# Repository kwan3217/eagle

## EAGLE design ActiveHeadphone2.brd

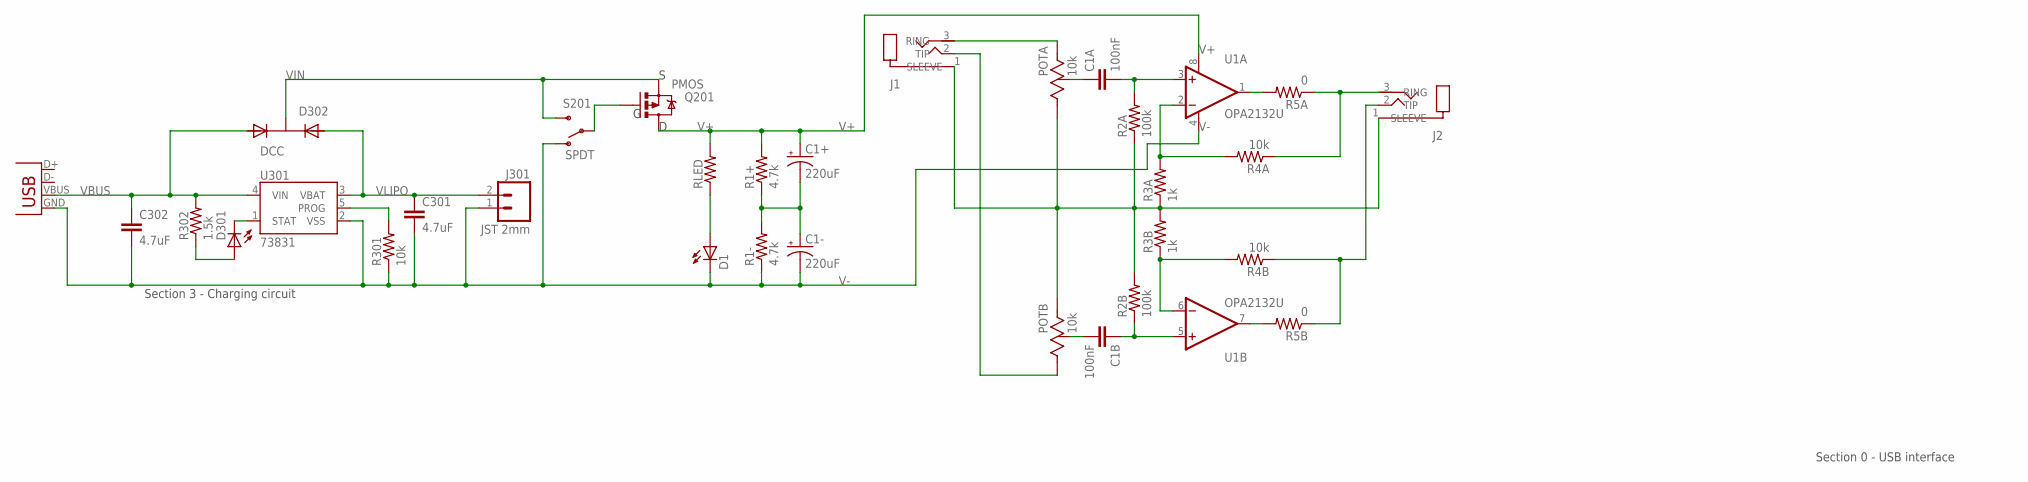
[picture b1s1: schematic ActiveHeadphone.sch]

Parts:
C1+, C1-: 220uF; EIA7343; DIGIKEY 399-5124-1-ND
C1A, C1B: 100nF; 0603-CAP
C301, C302: 4.7uF; 0603-CAP
D1, D301: RED; LED-0603
D302: DCC; SOT-23-3
J1, J2: 3.5mm; SJ1-3513-SMT
J003: USBSMD; USB-MINIB
J301: JST 2mm; JST-2-SMD
POTA: 10k; 3352T
POTB: 10k; 3352T
Q201: PMOS; SOT23-3
R1+, R1-: 4.7k; 0603-RES
R2A, R2B: 100k; 0603-RES
R3A, R3B: 1k; 0603-RES
R4A, R4B, R301: 10k; 0603-RES
R5A, R5B: 0; 0603-RES
R302: 1.5k; 0603-RES
RLED: RESISTOR0603-RES; 0603-RES
S201: SPDT; AYZ0202
U1: OPA2132U; SO08
U301: 73831; SOT23-5

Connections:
unnamed: C1A.2, R2A.2, U1.3 (+IN)
unnamed: D1.A, RLED.1
unnamed: J2.3 (RING), R4A.1, R5A.1
unnamed: J1.3 (RING), POTA.3 (CW)
unnamed: C1A.1, POTA.2 (WIPER)
unnamed: R5A.2, U1.1 (OUT)
unnamed: R3A.2, R4A.2, U1.2 (-IN)
unnamed: J1.2 (TIP), POTB.1 (CCW)
unnamed: C1B.2, POTB.2 (WIPER)
unnamed: C1B.1, R2B.1, U1.5 (+IN)
unnamed: R3B.1, R4B.2, U1.6 (-IN)
unnamed: R5B.2, U1.7 (OUT)
unnamed: J2.2 (TIP), R4B.1, R5B.1
unnamed: R301.2, U301.5 (PROG)
unnamed: C1+.C (-), C1-.A (+), R1+.1, R1-.2
unnamed: Q201.1 (G), S201.2
unnamed: D301.A, R302.1
unnamed: D301.C, U301.1 (STAT)
V+: C1+.A (+), Q201.3 (D), R1+.2, RLED.2, U1.8 (V+)
V-: C1-.C (-), C301.2, C302.2, D1.C, J003.GND, J301.1, R1-.1, R301.1, S201.1 (O), U1.4 (V-), U301.2 (VSS)
VBUS: C302.1, D302.1 (A1), J003.VBUS, R302.2, U301.4 (VIN)
VGND: J1.1 (SLEEVE), J2.1 (SLEEVE), POTA.1 (CCW), POTB.3 (CW), R2A.1, R2B.2, R3A.1, R3B.2
VIN: D302.3 (K), Q201.2 (S), S201.3 (S)
VLIPO: C301.1, D302.2 (A2), J301.2, U301.3 (VBAT)

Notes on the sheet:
Section 3 - Charging circuit
Section 0 - USB interface

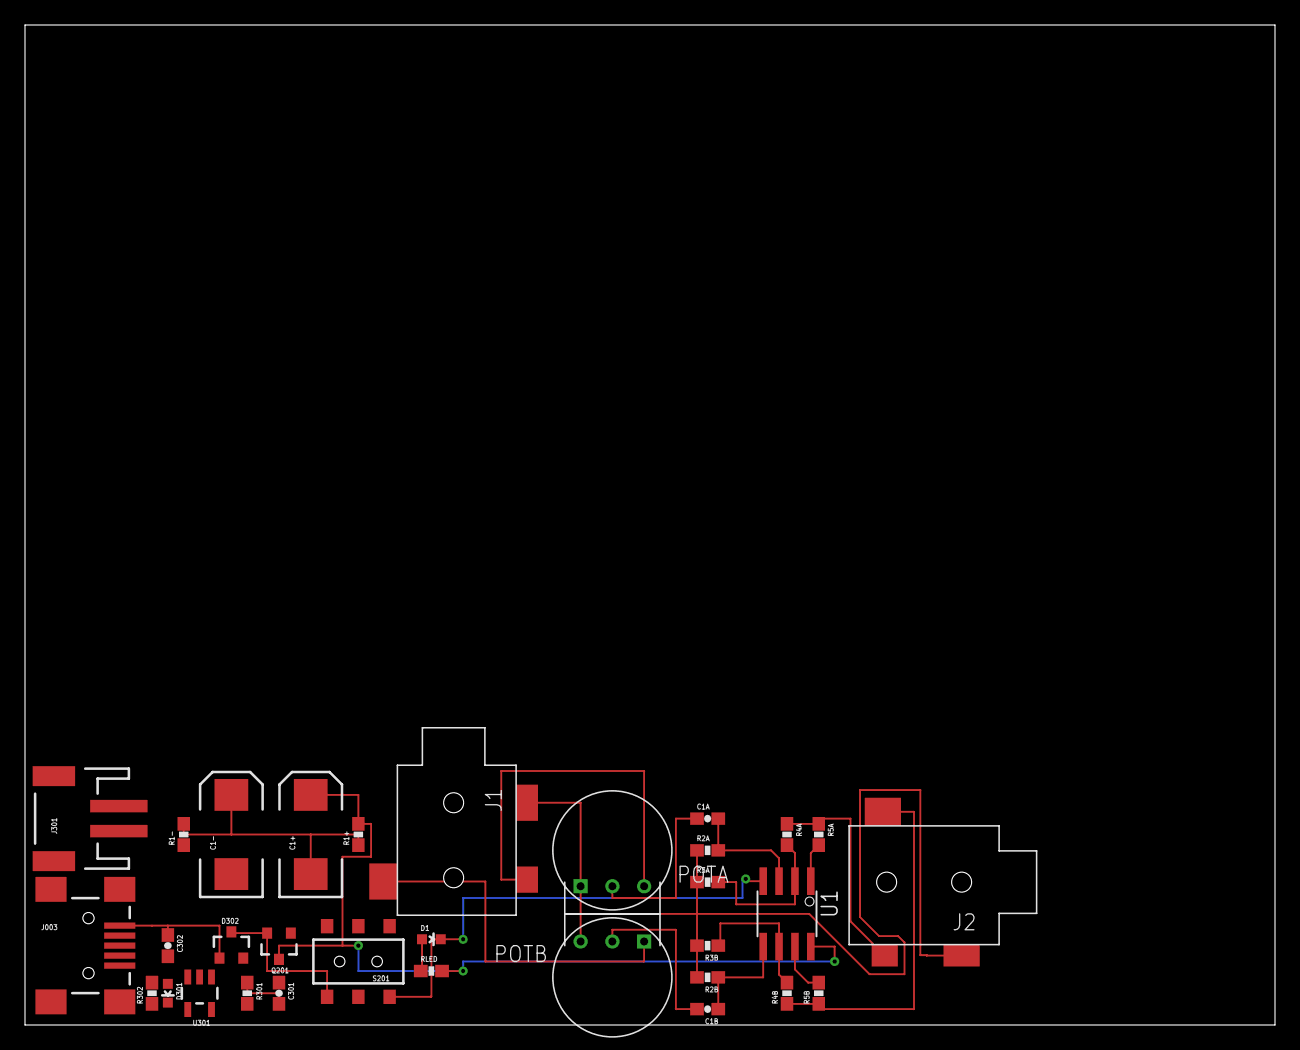
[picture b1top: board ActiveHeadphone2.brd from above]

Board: 2 copper layers, 100.0 x 80.0 mm, 32 parts (0 on the bottom side), 24 nets.

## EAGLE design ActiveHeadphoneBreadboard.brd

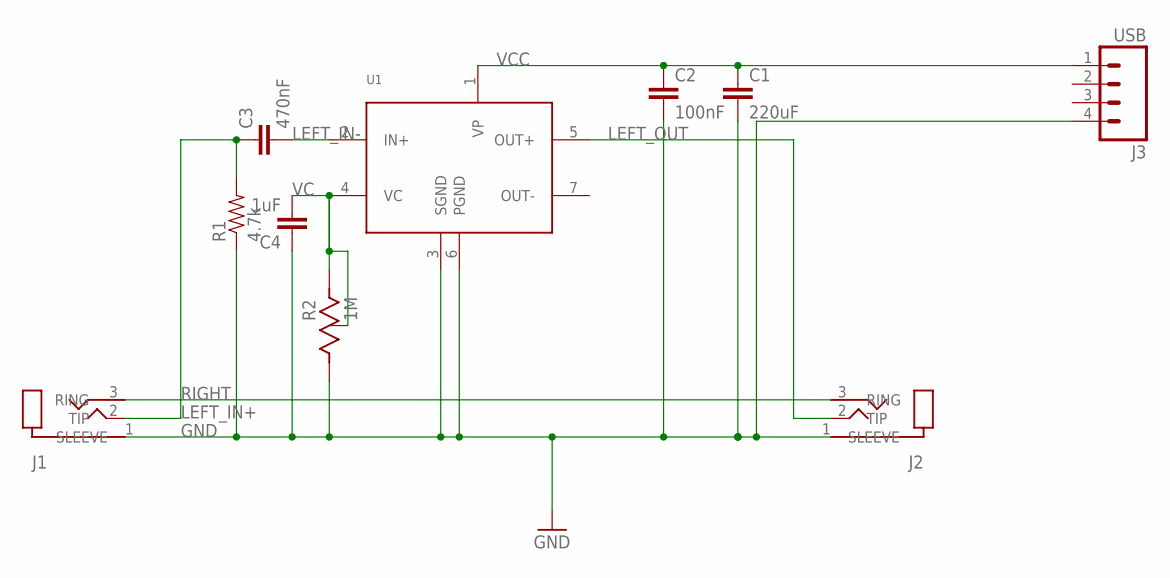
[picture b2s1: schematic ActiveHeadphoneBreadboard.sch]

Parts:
C1: 220uF; CAP-PTH-5MM
C2: 100nF; CAP-PTH-5MM
C3: 470nF; CAP-PTH-SMALL
C4: 1uF; CAP-PTH-SMALL
J1, J2: SJ1-35XXPTH; SJ1-3523N
J3: USB; 1X04
R1: 4.7k; AXIAL-0.4
R2: 1M; 3352T
U1: TDA7052; DIL-8

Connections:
GND: C1.2, C2.2, C4.1, J1.1 (SLEEVE), J2.1 (SLEEVE), J3.4, R1.P$1 (1), R2.1 (CCW), U1.3 (SGND), U1.6 (PGND)
LEFT_IN+: C3.1, J1.2 (TIP), R1.P$2 (2)
LEFT_IN-: C3.2, U1.2 (IN+)
LEFT_OUT: J2.2 (TIP), U1.5 (OUT+)
RIGHT: J1.3 (RING), J2.3 (RING)
VC: C4.2, R2.2 (WIPER), R2.3 (CW), U1.4 (VC)
VCC: C1.1, C2.1, J3.1, U1.1 (VP)

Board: 2 copper layers, 10 parts (0 on the bottom side), 7 nets, no tracks yet.

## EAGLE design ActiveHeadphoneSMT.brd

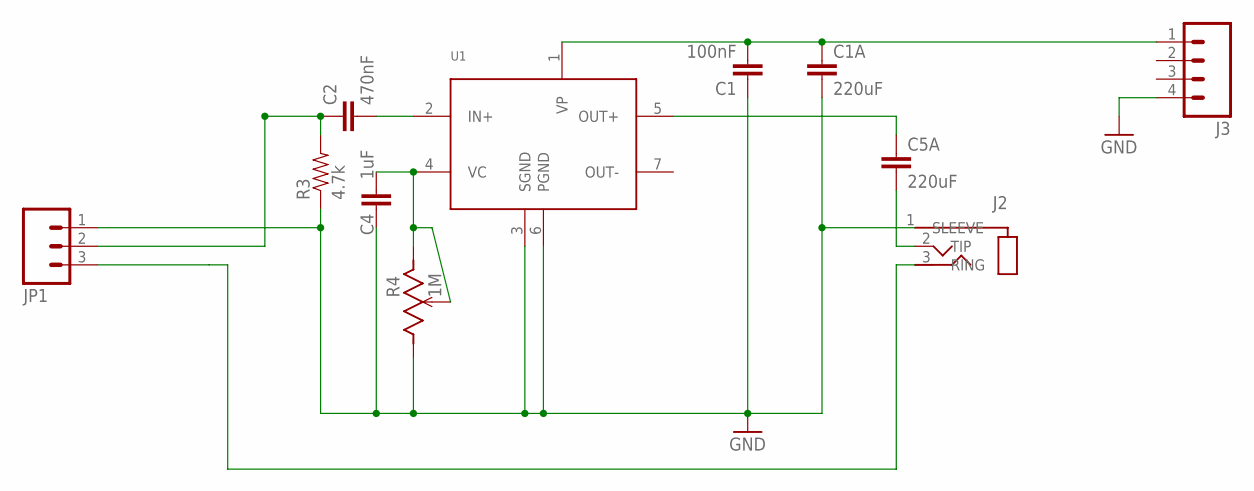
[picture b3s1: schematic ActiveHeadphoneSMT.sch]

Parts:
C1: 100nF; 0603-CAP
C1A, C5A: 220uF; CAP-PTH-5MM
C2: 470nF; 0603-CAP
C4: 1uF; 0603-CAP
J2: SJ1-35XXPTH; SJ1-3523N
J3: M04PTH; 1X04
JP1: M03PTH; 1X03
R3: 4.7k; 0603-RES
R4: 1M; 3352T
U1: TDA7052; DIL-8

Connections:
GND: C1.1, C1A.2, C4.1, J2.1 (SLEEVE), J3.4, JP1.1, R3.1, R4.1 (CCW), U1.3 (SGND), U1.6 (PGND)
unnamed: C2.2, U1.2 (IN+)
unnamed: C2.1, JP1.2, R3.2
unnamed: C5A.2, J2.2 (TIP)
unnamed: C4.2, R4.2 (WIPER), R4.3 (CW), U1.4 (VC)
unnamed: C1.2, C1A.1, J3.1, U1.1 (VP)
unnamed: C5A.1, U1.5 (OUT+)
unnamed: J2.3 (RING), JP1.3

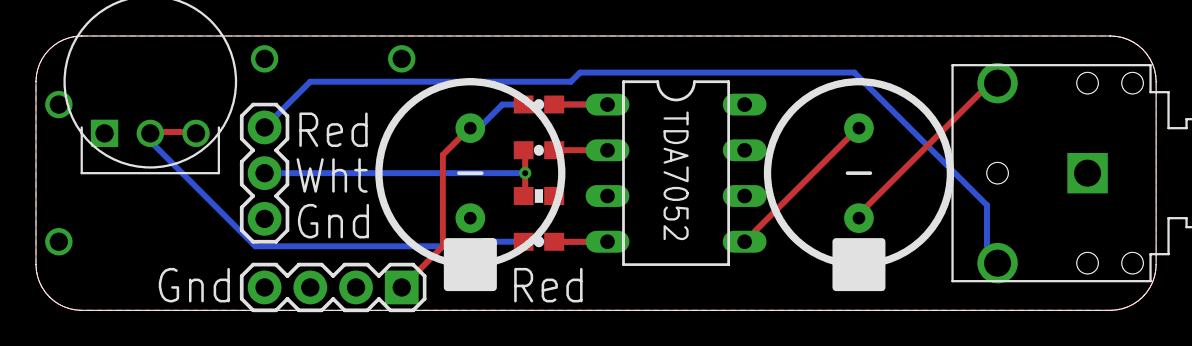
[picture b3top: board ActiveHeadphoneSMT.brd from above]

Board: 2 copper layers, 62.2 x 15.2 mm, 12 parts (1 on the bottom side), 8 nets.

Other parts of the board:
U$1: KWAN_CIRCLE

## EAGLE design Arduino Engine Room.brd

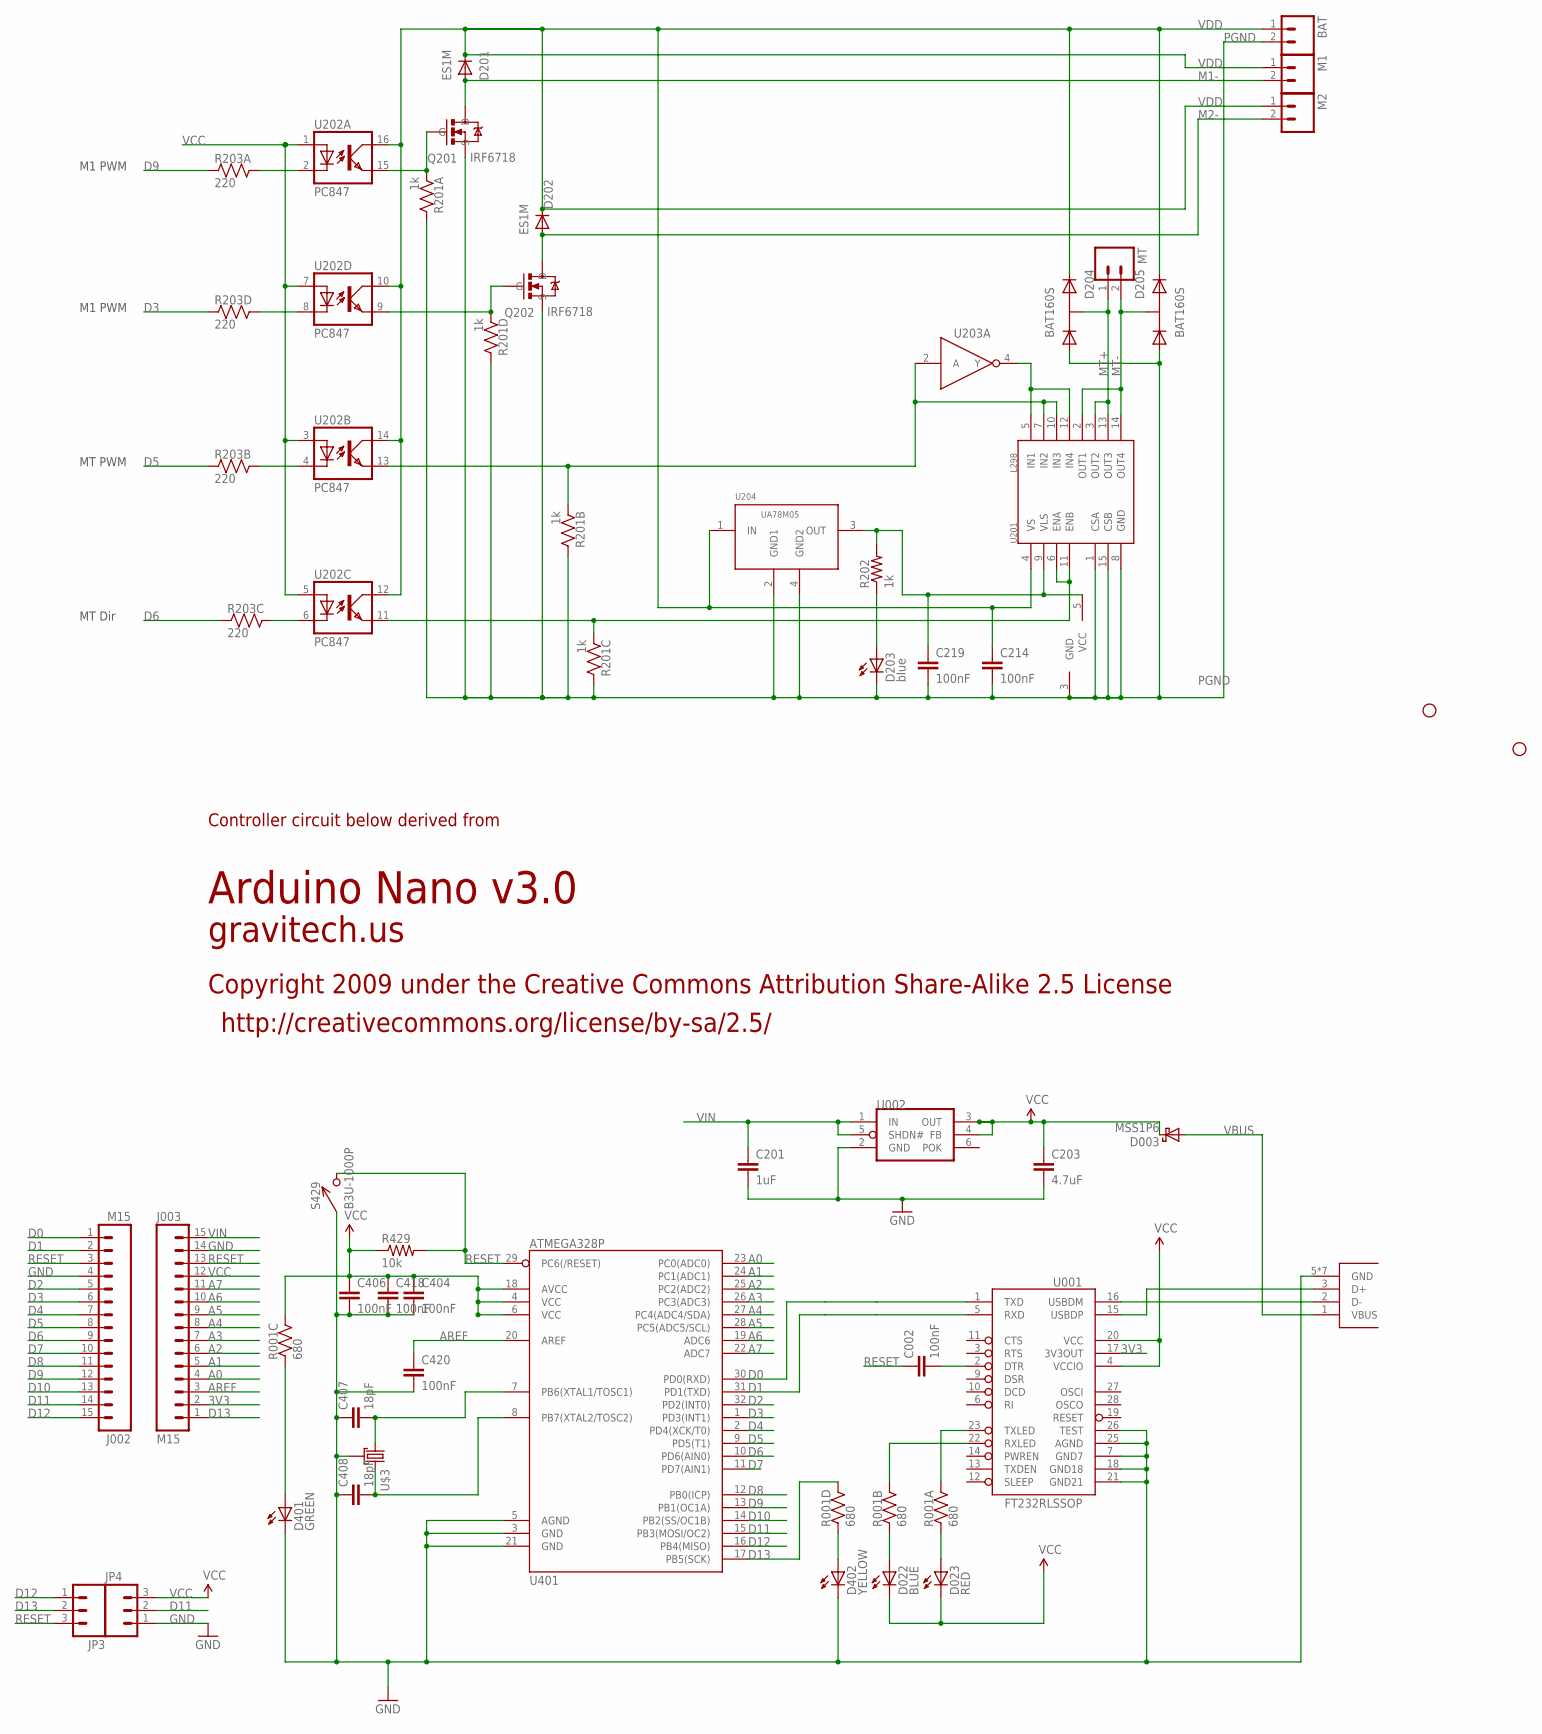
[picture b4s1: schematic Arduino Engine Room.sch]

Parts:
BAT: M02PTH4; 1X02_XTRA_BIG
C002, C404, C406, C418, C420: 100nF; 0402-CAP; DIGIKEY 445-1268-1-ND
C201: 1uF; 0402-CAP; DIGIKEY 445-1415-1-ND
C203: 4.7uF; 0402-CAP; DIGIKEY 445-7395-1-ND
C214, C219: 100nF; 0402-CAP
C407, C408: 18pF; 0402-CAP; DIGIKEY 445-1238-1-ND
D003: MSS1P6; MICROSMP; DIGIKEY MSS1P6-M3/89AGICT-ND
D022: BLUE; LED-0603; DIGIKEY 350-2037-1-ND
D023: RED; LED-0603; DIGIKEY 754-1359-1-ND
D201, D202: ES1M; DO-214AC
D203: blue; LED-0603
D204, D205: BAT160S; SOT-223
D401: GREEN; LED-0603; DIGIKEY 350-2036-1-ND
D402: YELLOW; LED-0603; DIGIKEY 754-1124-1-ND
J001: USB_MICROB_JST; UB-MC5BR3-SD204-4S; DIGIKEY 455-2562-1-ND
J002, J003: M15; 1X15; DIGIKEY $NOPART
JP1, JP2: STAND-OFF
JP3, JP4: M03PTH; 1X03; DIGIKEY $NOPART
M1, M2: M02PTH4; 1X02_XTRA_BIG
MT: M02PTH; 1X02
Q201, Q202: IRF6718; DIRECTFET_L6
R001: 680; CRA04; DIGIKEY CRA4S8680CT-ND
R201: 1k; CRA04
R202: 1k; 0402-RES
R203: 220; CRA04
R429: 10k; 0402-RES; DIGIKEY P10.0KLCT-ND
S429: B3U-1000P
U001: FT232RLSSOP; SSOP28DB; DIGIKEY 768-1007-1-ND
U002: MAX8881; SOT-23-6; DIGIKEY MAX8881EUT50+TCT-ND
U201: L298; MULTIWATT15
U202: PC847; DIL16
U203: MC74VHC1G04; SOT-23-5
U204: UA78M05; SOT223
U401: ATMEGA328P; TQFP32-08; DIGIKEY ATMEGA328P-15AZCT-ND
U$3: CX2520; CRYSTAL_SMD_2MM_2_5MM

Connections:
3V3: J003.2, U001.17 (3V3OUT)
A0: J003.4, U401.23 (PC0(ADC0))
A1: J003.5, U401.24 (PC1(ADC1))
A2: J003.6, U401.25 (PC2(ADC2))
A3: J003.7, U401.26 (PC3(ADC3))
A4: J003.8, U401.27 (PC4(ADC4/SDA))
A5: J003.9, U401.28 (PC5(ADC5/SCL))
A6: J003.10, U401.19 (ADC6)
A7: J003.11, U401.22 (ADC7)
AREF: C420.1, J003.3, U401.20 (AREF)
D0: J002.1, U001.1 (TXD), U401.30 (PD0(RXD))
D1: J002.2, U001.5 (RXD), U401.31 (PD1(TXD))
D2: J002.5, U401.32 (PD2(INT0))
D3: J002.6, R203.4 (1), U401.1 (PD3(INT1))
D4: J002.7, U401.2 (PD4(XCK/T0))
D5: J002.8, R203.2 (1), U401.9 (PD5(T1))
D6: J002.9, R203.3 (1), U401.10 (PD6(AIN0))
D7: J002.10, U401.11 (PD7(AIN1))
D8: J002.11, U401.12 (PB0(ICP))
D9: J002.12, R203.1, U401.13 (PB1(OC1A))
D10: J002.13, U401.14 (PB2(SS/OC1B))
D11: J002.14, JP4.2, U401.15 (PB3(MOSI/OC2))
D12: J002.15, JP3.1, U401.16 (PB4(MISO))
D13: J003.1, JP3.2, R001.5 (2), U401.17 (PB5(SCK))
DTR#: C002.2, U001.2 (DTR)
GND: C201.2, C203.2, C404.2, C406.2, C407.1, C408.1, C418.2, C420.2, D401.C, D402.C, J001.5 (GND), J001.P$1, J001.P$2, J001.P$3, J001.P$4, J001.P$8 (GND), J001.P$10 (GND), J002.4, J003.14, JP4.1, S429.P$1 (1), U001.7 (GND7), U001.18 (GND18), U001.21 (GND21), U001.25 (AGND), U001.26 (TEST), U002.2 (GND), U401.3 (GND), U401.5 (AGND), U401.21 (GND), U$3.2, U$3.4
M1-: D201.A, M1.2, Q201.D1 (D), Q201.D2 (D)
M2-: D202.A, M2.2, Q202.D1 (D), Q202.D2 (D)
MT+: D204.4 (K1A2), MT.1, U201.3 (OUT2), U201.13 (OUT3)
MT-: D205.4 (K1A2), MT.2, U201.2 (OUT1), U201.14 (OUT4)
unnamed: D203.A, R202.1
unnamed: U201.5 (IN1), U201.12 (IN4), U203.4 (Y)
unnamed: C407.2, U401.7 (PB6(XTAL1/TOSC1)), U$3.1
unnamed: C408.2, U401.8 (PB7(XTAL2/TOSC2)), U$3.3 (2)
unnamed: J001.3 (D+), U001.15 (USBDP)
unnamed: J001.2 (D-), U001.16 (USBDM)
unnamed: D401.A, R001.3 (1)
unnamed: D402.A, R001.4 (1)
unnamed: D023.A, R001.1
unnamed: C219.1, R202.2, U201.9 (VLS), U203.5 (VCC), U204.3 (OUT)
unnamed: D022.A, R001.2 (1)
unnamed: R201.3 (1), U201.6 (ENA), U201.11 (ENB), U202.11 (EMIT)
unnamed: R203.8 (2), U202.2 (C)
unnamed: R203.5 (2), U202.8 (C)
unnamed: R203.7 (2), U202.4 (C)
unnamed: R203.6 (2), U202.6 (C)
unnamed: Q201.G, R201.1, U202.15 (EMIT)
unnamed: Q202.G, R201.4 (1), U202.9 (EMIT)
unnamed: R201.2 (1), U201.7 (IN2), U201.10 (IN3), U202.13 (EMIT), U203.2 (A)
PGND: BAT.2, C214.2, C219.2, D203.C, D204.1 (A1), D205.1 (A1), Q201.S, Q202.S, R201.5 (2), R201.6 (2), R201.7 (2), R201.8 (2), U201.1 (CSA), U201.8 (GND), U201.15 (CSB), U203.3 (GND), U204.2 (GND1), U204.4 (GND2)
RESET: C002.1, J002.3, J003.13, JP3.3, R429.2, S429.P$2 (2), U401.29 (PC6(/RESET))
RXLED1: R001.7 (2), U001.22 (RXLED)
TXLED1: R001.8 (2), U001.23 (TXLED)
VBUS: D003.A, J001.1 (VBUS)
VCC: C203.1, C404.1, C406.1, C418.1, D003.K, D022.C, D023.C, J003.12, JP4.3, R001.6 (2), R429.1, U001.4 (VCCIO), U001.20 (VCC), U002.3 (OUT), U002.4 (FB), U202.1 (A), U202.3 (A), U202.5 (A), U202.7 (A), U401.4 (VCC), U401.6 (VCC), U401.18 (AVCC)
VDD: BAT.1, C214.1, D201.C, D202.C, D204.3 (K2), D205.3 (K2), M1.1, M2.1, U201.4 (VS), U202.10 (COL), U202.12 (COL), U202.14 (COL), U202.16 (COL), U204.1 (IN)
VIN: C201.1, J003.15, U002.1 (IN), U002.5 (SHDN#)

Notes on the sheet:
Arduino Nano v3.0
Copyright 2009 under the Creative Commons Attribution Share-Alike 2.5 License
http://creativecommons.org/license/by-sa/2.5/
Controller circuit below derived from
gravitech.us
M1 PWM
MT Dir
MT PWM

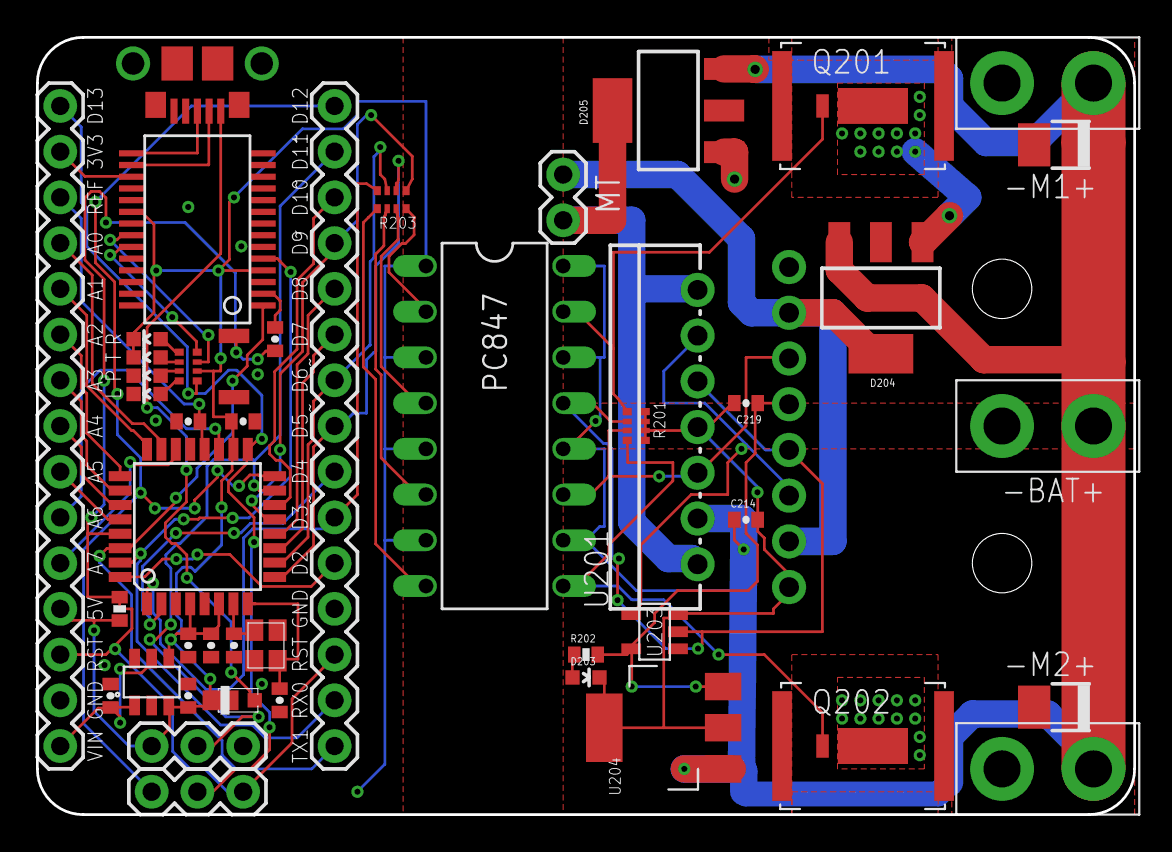
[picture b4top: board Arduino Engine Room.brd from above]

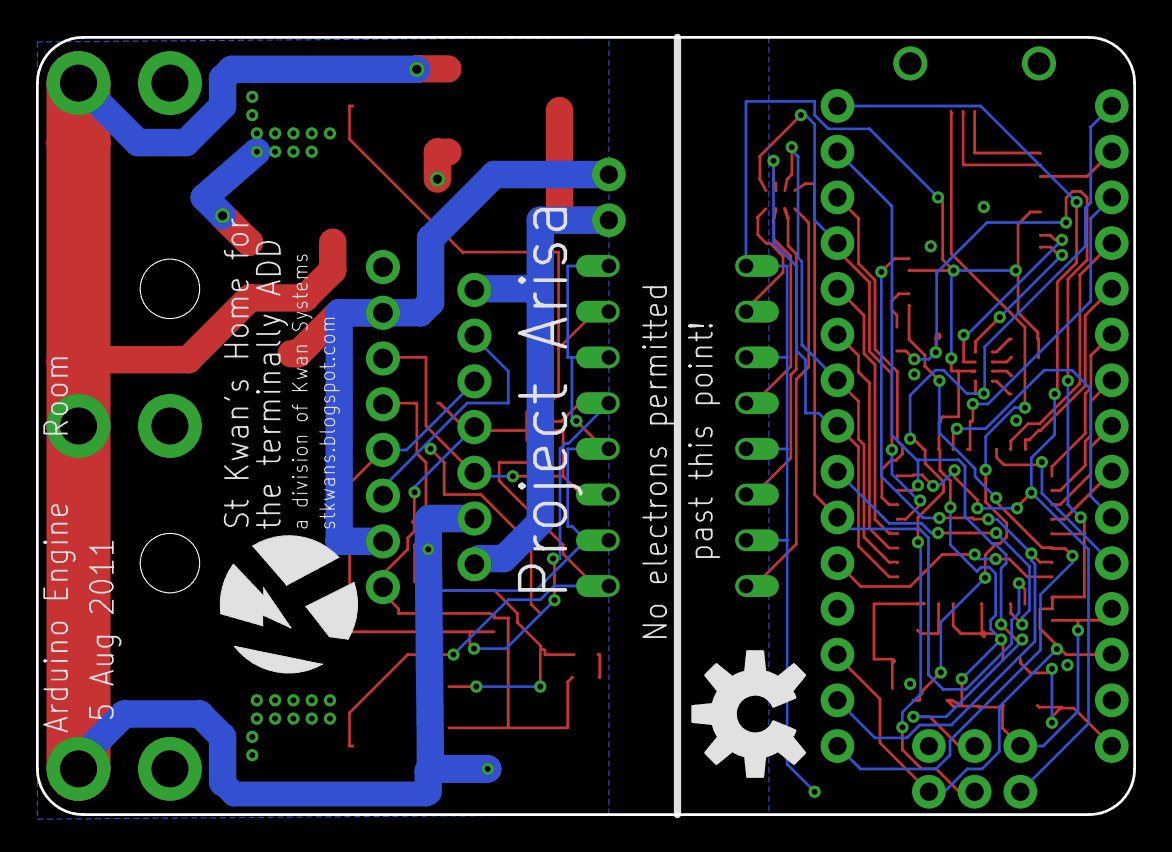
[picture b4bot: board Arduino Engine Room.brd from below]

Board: 2 copper layers, 61.0 x 43.2 mm, 50 parts (2 on the bottom side), 57 nets.

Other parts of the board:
U$1: KWAN_CIRCLE
U$2: OSHW-LOGO-L

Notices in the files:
parts and their libraries:
SparkFun: Licensing: CC v3.0 Share-Alike You are welcome to use this library for commercial purposes.
